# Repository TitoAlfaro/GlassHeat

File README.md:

GlassHeat
=========

Linking a Peltier to the Glass Infrastructure at the Media Lab.

Translating location information to temperature against the skin, I'll test how the body can respond to different data to create awareness of the surrounding context.

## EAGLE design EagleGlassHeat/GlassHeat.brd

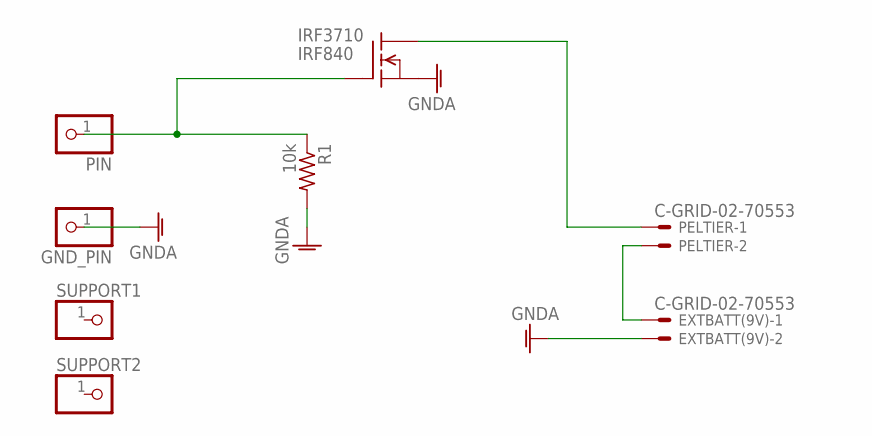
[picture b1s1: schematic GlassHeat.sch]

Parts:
EXTBATT(9V): C-GRID-02-70553; 70553-02
GND_PIN: PINHD-1X1; 1X01
IRF3710: IRF840; TO220
PELTIER: C-GRID-02-70553; 70553-02
PIN: PINHD-1X1; 1X01
R1: 10k; 0207/7
SUPPORT1, SUPPORT2: PINHD-1X1; 1X01

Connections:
GNDA: EXTBATT(9V).2, GND_PIN.1, IRF3710.3 (S), R1.2
unnamed: IRF3710.1 (G), PIN.1, R1.1
unnamed: IRF3710.2 (D), PELTIER.1
unnamed: EXTBATT(9V).1, PELTIER.2

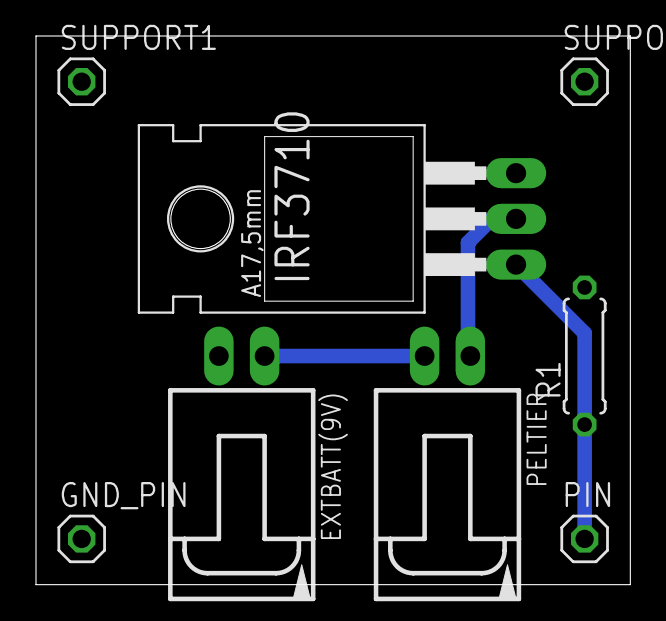
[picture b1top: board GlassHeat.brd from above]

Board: 2 copper layers, 33.0 x 30.5 mm, 8 parts (0 on the bottom side), 4 nets.

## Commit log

2013-06-19 ADDED Glass feed back
    Need to work on controlling the Peltier.
2013-06-20 Consolidated
2013-06-21 Peltier and PWM Working
2013-06-25 Changed name to GlassHeatMain
2013-07-03 STABLE
2013-07-09 MAJOR: REFACTOR: reworking entire code base to be more modular and clear.
2013-07-10 minor
2013-07-10 DELETED: several files that were not needed anymore.
    REFACTOR: playing with making IOIOGlassHeatService more generic, might
    not make any sense...we will see what comes to pass.
2013-07-16 After merge, some minor issues
2013-07-17 The IOIO service never stops and interferes with other apps that use IOIO
2013-07-17 Still not fixed the IOIO service never stopping
2013-07-17 FIXED: Was not diconnecting from ioio board correctly when stoping IOIOService, now we are. CHANGED: notification code to be called only if IOIO is connected, not if the service is stared since the s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
2013-07-17 added .gitignore file so we don't track bin etc.
2013-07-17 REMOVED: bin directory and files from repo.
2013-07-18 Added a GitIgnore and a gitattributes
2013-07-18 After Merging again with new bin (I guess)
2013-07-18 UPDATED: android-support-v4.jar to android-support-v13.jar
2013-07-18 FIX: BUG: forgot to properly initiate notification manager var in IOIOGlassHeatService.
2013-07-18 FIX: had issues with minSdkVersion to low for notification menu stuff. fixed that and now it works.
2013-07-18 REMOVED: import statemnts that were not used in IOIOGlassHeatService
2013-07-18 Commit before Pull
    Fixed merged IOIO glass heat service
2013-07-24 BROKEN: playing wiht wifi detection
2013-07-25 config file changes
2013-07-25 add code to find what glass the desired person is at
2013-07-26 try to fix micah's mess
2013-07-26 ADDED: Pseudo code for the Matrix operation.
2013-08-06 ADDED: distance matrix, still testing accuracy
2013-08-06 tested accuracy, worked with Tangible screen
2013-08-06 adde the heatDistance variable
2013-08-06 CHANGE: to project.properties for micah's paths
2013-08-06 ADDED: new code to handel distance heat value to IOIO
2013-08-06 heatDistance updates the seekbar value
2013-08-08 STABLE: works aroudn the lab and with the debug button
2014-03-24 Coomit
2014-04-28 Clone to samsung Added eagle
